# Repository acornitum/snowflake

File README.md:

# Snowflake - one key macropad

Snowflake is a one key macropad! Solder on any mx-style switch and use it as a one key keyboard - the PCB itself measures 19x19mm :D

Featuring: 

- CH552E as the microcontroller
- Neopixel on the bottom
- All unused pins broken out
- USB-C for power and data
- Keychain hole (M2 screw size); hang it on your bag!

This project was made in ~5h in one go, art included.

I've ordered 160 of these - at that quantity, when panelized, they cost <1.5 USD each, parts and assembly included. I'll be giving them out - if you see me IRL, feel free to ask for one!

Screenshot of schematic + PCB in KiCad: 

This repo will be updated with a 3d printable case later :D

For uploading your own firmware, go to the readme in the firmware folder of this repo!

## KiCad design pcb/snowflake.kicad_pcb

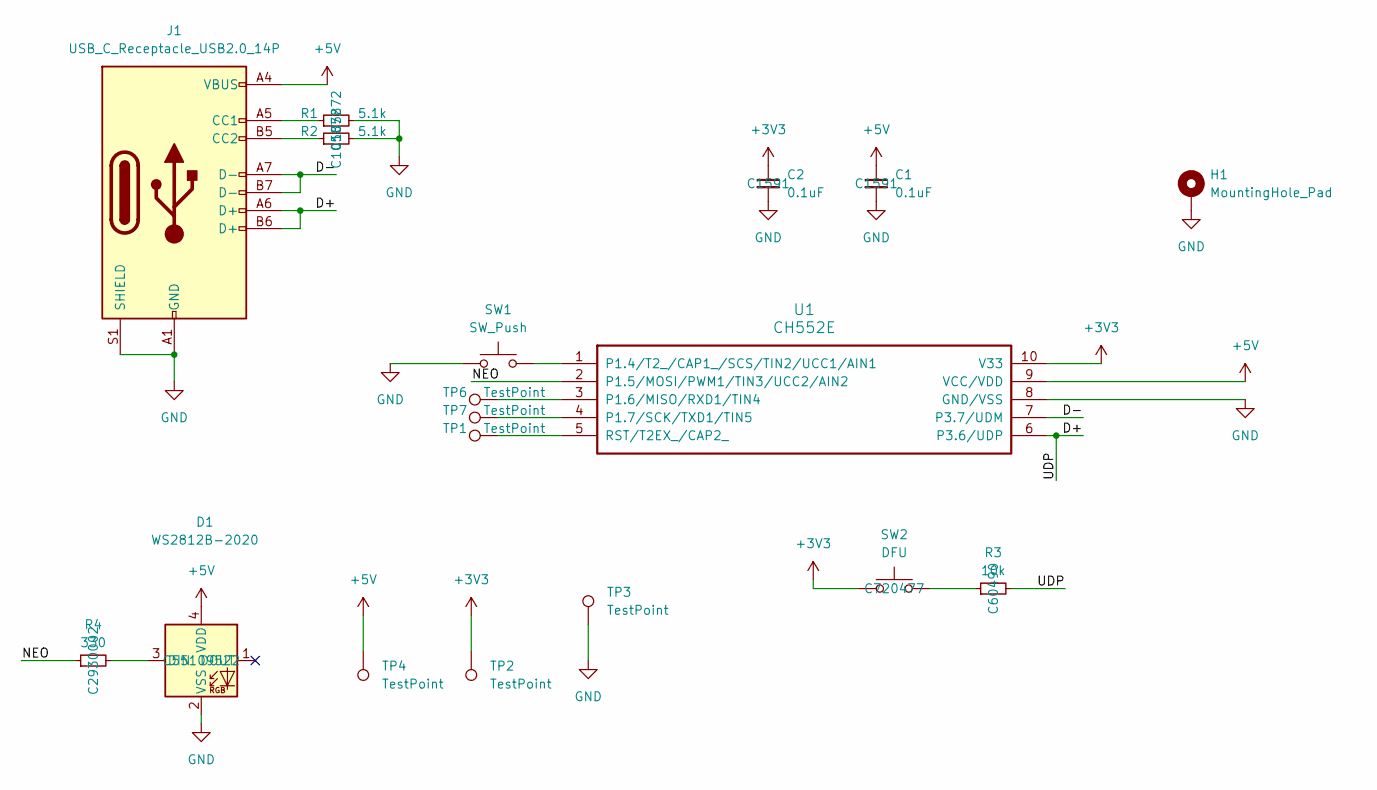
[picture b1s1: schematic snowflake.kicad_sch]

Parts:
C1, C2: 0.1uF; C_0603_1608Metric; LCSC C1591
D1: WS2812B-2020; LED_WS2812B-2020_PLCC4_2.0x2.0mm; LCSC C55109522
H1: MountingHole_Pad; MountingHole_2.2mm_M2_DIN965_Pad
J1: USB_C_Receptacle_USB2.0_14P; USB_C_Receptacle_HRO_TYPE-C-31-M-12; LCSC C393939
R1, R2: 5.1k; R_0402_1005Metric; LCSC C105872
R3: 10k; R_0402_1005Metric; LCSC C60490
R4: 330; R_0402_1005Metric; LCSC C2930002
SW1: SW_Push; SW_Cherry_MX_1.00u_PCB
SW2: DFU; SW_Push_SPST_NO_Alps_SKRK; LCSC C720477
TP1, TP2, TP3, TP4, TP6, TP7: TestPoint; TestPoint_Pad_D1.5mm
U1: CH552E; MSOP-10_3x3mm_P0.5mm; LCSC C967938

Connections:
+3V3: C2.1, SW2.1, TP2.1, U1.10 (V33)
+5V: C1.1, D1.4 (VDD), J1.A4 (VBUS), J1.A9 (VBUS), J1.B4 (VBUS), J1.B9 (VBUS), TP4.1, U1.9 (VCC/VDD)
/D+: J1.A6 (D+), J1.B6 (D+), R3.2, U1.6 (P3.6/UDP)
/D-: J1.A7 (D-), J1.B7 (D-), U1.7 (P3.7/UDM)
/NEO: R4.1, U1.2 (P1.5/MOSI/PWM1/TIN3/UCC2/AIN2)
GND: C1.2, C2.2, D1.2 (VSS), H1.1, J1.A1 (GND), J1.A12 (GND), J1.B1 (GND), J1.B12 (GND), J1.S1 (SHIELD), R1.2, R2.2, SW1.1, TP3.1, U1.8 (GND/VSS)
unnamed: D1.3 (DIN), R4.2
unnamed: J1.A5 (CC1), R1.1
unnamed: J1.B5 (CC2), R2.1
unnamed: R3.1, SW2.2
unnamed: SW1.2, U1.1 (P1.4/T2_/CAP1_/SCS/TIN2/UCC1/AIN1)
unnamed: TP6.1, U1.3 (P1.6/MISO/RXD1/TIN4)
unnamed: TP7.1, U1.4 (P1.7/SCK/TXD1/TIN5)
unnamed: TP1.1, U1.5 (RST/T2EX_/CAP2_)

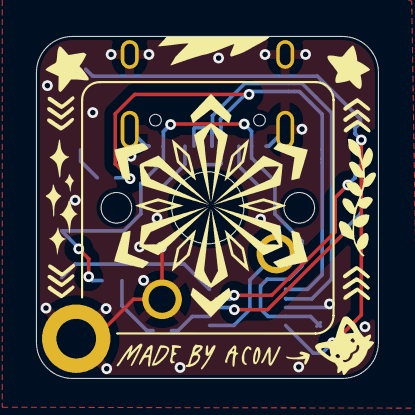
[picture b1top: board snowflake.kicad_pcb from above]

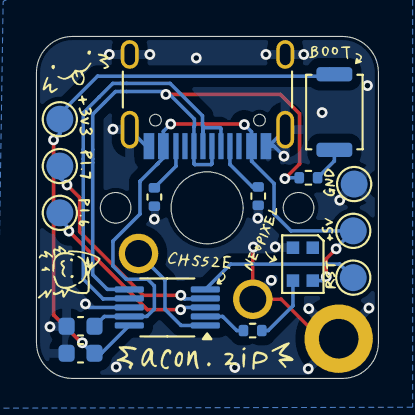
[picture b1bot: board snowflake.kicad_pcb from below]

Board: 2 copper layers, 19.0 x 19.0 mm, 18 parts (16 on the bottom side), 14 nets.
